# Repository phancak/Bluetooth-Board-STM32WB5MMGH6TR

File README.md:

# STM32WB5MMGH6TR Bluetooth Expansion Board  

## Overview  
This project features a **Bluetooth expansion board** based on the **STM32WB5MMGH6TR module**, designed for seamless integration with various embedded systems. The board provides flexible connectivity through **I2C, USART, and SPI**, making it an ideal solution for rapid prototyping and system expansion.  

Engineered for **low-power applications** and **high-performance wireless communication**, this board serves as a versatile platform for **IoT, industrial automation, and smart embedded devices**.  

## Features  
✅ **STM32WB5MMGH6TR Module** – Dual-core Cortex-M4/M0+ with BLE 5.2 support  
✅ **Multiple Communication Interfaces** – I2C, USART, and SPI for seamless integration  
✅ **Compact and Modular Design** – Easily integrates with other MCU-based projects  
✅ **Low-Power Optimization** – Suitable for battery-powered applications  
✅ **Expandable & Customizable** – Compatible with additional peripherals  

## Applications  
- **IoT Devices** – Wireless sensors, smart home automation  
- **Industrial Monitoring** – Data acquisition, remote control systems  
- **Embedded Systems Development** – Ideal for prototyping and experimentation  

## Getting Started  
### Hardware Requirements  
- STM32WB5MMGH6TR Bluetooth Expansion Board  
- Host MCU (STM32, ESP32, etc.)  
- Power Supply (3.3V)  
- Serial Debugging Tools (USB-to-Serial Adapter)  

### Software Requirements  
- **STM32CubeIDE** – For firmware development  
- **STM32CubeWB** – Bluetooth stack and middleware  
- **Segger J-Link or ST-Link** – For debugging and flashing  

## Setup & Usage  
1. **Power the Board** – Provide 3.3V via USB or external power source.  
2. **Connect to Host MCU** – Use I2C, USART, or SPI for communication.  
3. **Flash Firmware** – Use STM32CubeIDE or STM32CubeProgrammer.  
4. **Test Bluetooth Functionality** – Verify BLE communication using a mobile app or a central device.  

## Repository Structure  
/Hardware        - PCB schematics and design files  
  /Schematic      - Circuit diagrams (PDF, KiCad, Altium, etc.)  
  /PCB            - Board layout files (Gerber, BOM, assembly files)  

## Future Enhancements  
- 🔹 **Additional Protocol Support** – Expanding compatibility with more peripherals  
- 🔹 **Power Optimization** – Fine-tuning sleep modes for ultra-low power consumption  
- 🔹 **Custom BLE Services** – Implementing advanced communication features  

## License  
This project is open-source under the **MIT License**.  

---

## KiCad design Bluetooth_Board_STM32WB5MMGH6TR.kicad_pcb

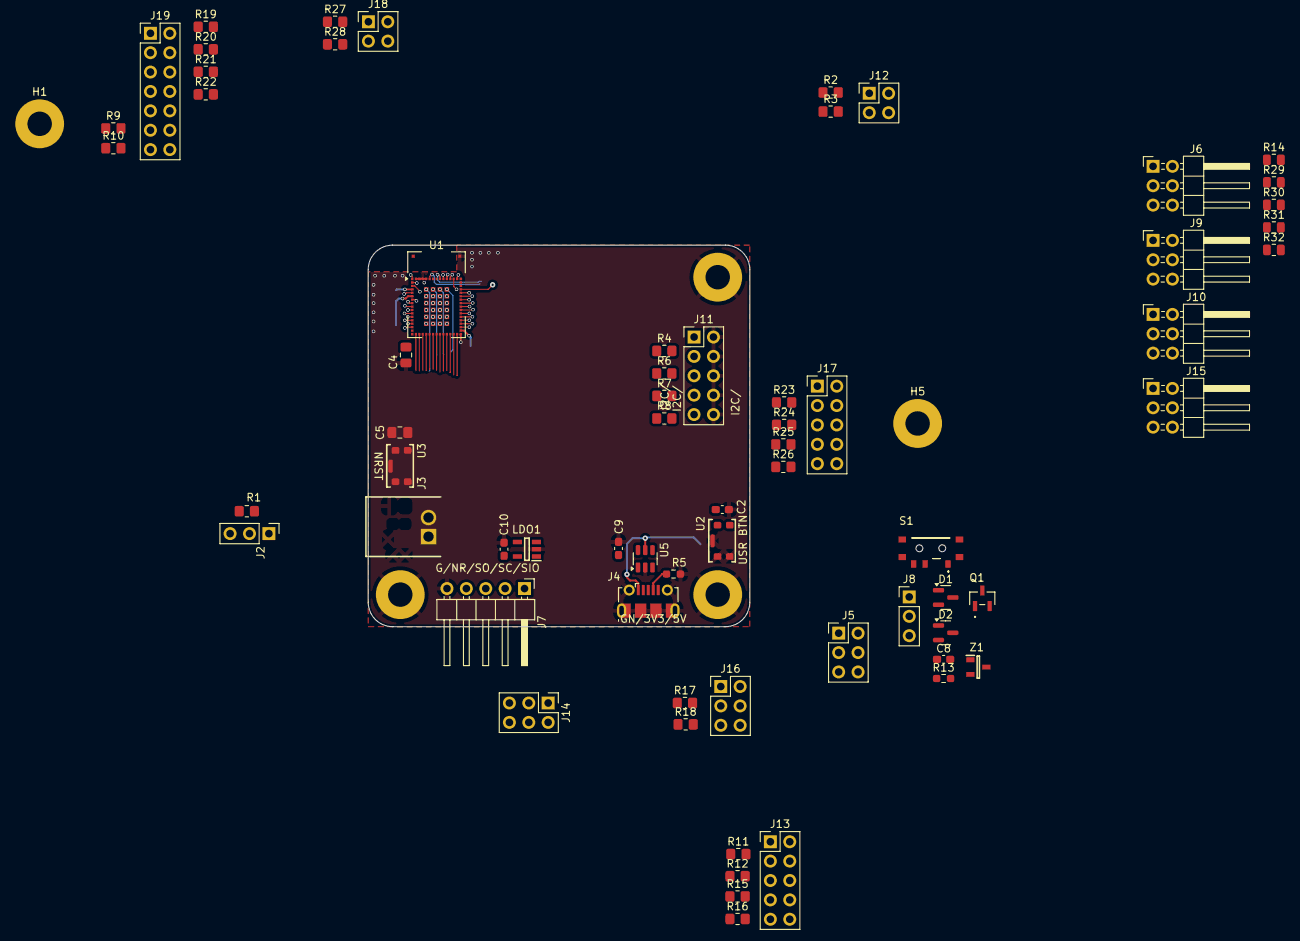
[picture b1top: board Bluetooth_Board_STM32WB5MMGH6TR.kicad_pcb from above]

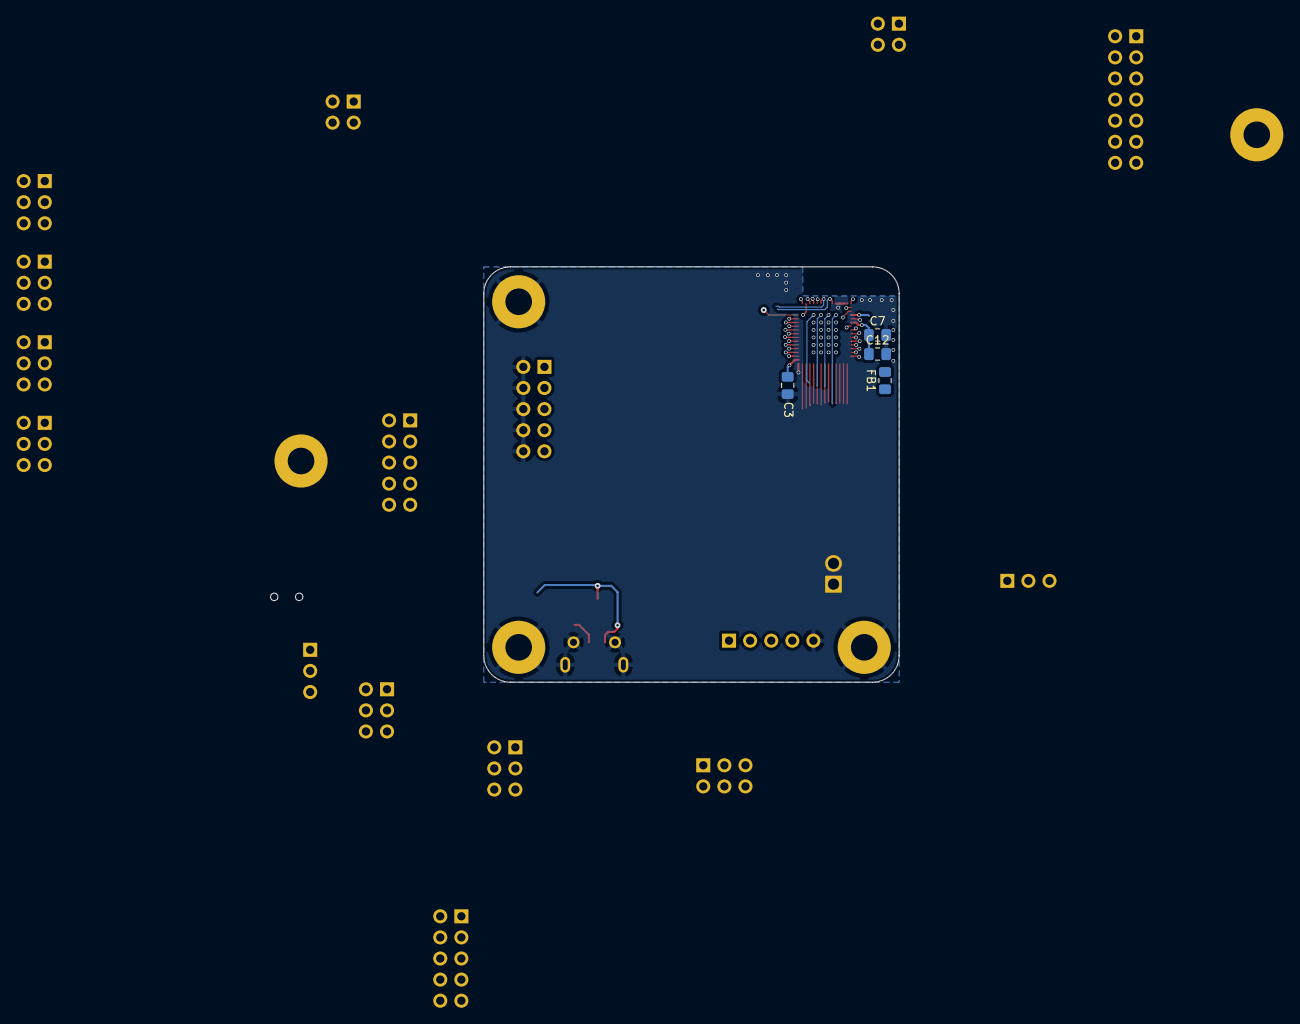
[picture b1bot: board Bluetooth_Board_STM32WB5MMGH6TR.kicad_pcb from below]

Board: 6 copper layers, 50.0 x 50.0 mm, 75 parts (4 on the bottom side), 79 nets.

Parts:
C2: 1uF; C_0603_1608Metric_Pad1.08x0.95mm_HandSolder
C3, C4, C7: 100n; C_0805_2012Metric_Pad1.18x1.45mm_HandSolder
C5: 100nF; C_0805_2012Metric_Pad1.18x1.45mm_HandSolder
C8: 4u7; C_0603_1608Metric_Pad1.08x0.95mm_HandSolder
C9, C10: 1u; C_0603_1608Metric_Pad1.08x0.95mm_HandSolder
C12: 4u7; C_0805_2012Metric_Pad1.18x1.45mm_HandSolder
D1: BZX84C4V3LT1G; SOT-23
D2: BZX84C6V2LT1G; SOT-23
FB1: BLM21PG601SN1D_0805; C_0805_2012Metric_Pad1.18x1.45mm_HandSolder
H1, H2, H3, H4, H5: MountingHole_Pad; MountingHole_3.2mm_M3_Pad
J2: BOOT0_Jumper; PinHeader_1x03_P2.54mm_Vertical
J3: JST_XH_2.54_Plug; Connector_Power2pin_SHDRRA2W80P0X250_1X2_740X1150X610P
J4: USB_B_Micro; USB_Micro-B_Molex-105017-0001
J5: Power_Selector_Jumper; PinHeader_2x03_P2.54mm_Vertical
J6: I2C1_Headers; PinHeader_2x03_P2.54mm_Horizontal
J7: SWD_Pins; PinHeader_1x05_P2.54mm_Horizontal
J8: 3V_Selection_Header; PinHeader_1x03_P2.54mm_Vertical
J9: LPUART1_Headers; PinHeader_2x03_P2.54mm_Horizontal
J10: SPI1_Headers; PinHeader_2x03_P2.54mm_Horizontal
J11: SPI1_Header; PinHeader_2x05_P2.54mm_Vertical
J12: TIM1_CH1_Headers; PinHeader_2x02_P2.54mm_Vertical
J13: SAI1_A_Header; PinHeader_2x05_P2.54mm_Vertical
J14: I2C1_Header; PinHeader_2x03_P2.54mm_Vertical
J15: General_Pin_Header; PinHeader_2x03_P2.54mm_Horizontal
J16: LPUART1_Header; PinHeader_2x03_P2.54mm_Vertical
J17: SAI1_B_Header; PinHeader_2x05_P2.54mm_Vertical
J18: ADC1_Headers; PinHeader_2x02_P2.54mm_Vertical
J19: QUADSPI_Header; PinHeader_2x07_P2.54mm_Vertical
LDO1: LDO_TLV75733PDBVR; LDO_SOT95P280X145-5N
Q1: MOSFET_SI2333DDS-T1-BE3; MOSFET_ SI2333DDS_SOT_DS-T1-BE3_VIS
R1: 1k; R_0805_2012Metric_Pad1.20x1.40mm_HandSolder
R2, R3, R4, R6, R7, R8, R9, R10, R11, R12, R15, R16, R17, R18, R19, R20, R21, R22, R23, R24, R25, R26, R27, R28: 100R; R_0805_2012Metric_Pad1.20x1.40mm_HandSolder
R5, R13: 100k; R_0603_1608Metric_Pad0.98x0.95mm_HandSolder
R14, R29, R30, R31, R32: 33R; R_0805_2012Metric
S1: Switch_WS-SLSU SMT Mini Slide
U1: STM32WB5MMGH6TR; ST-SiP-LGA-86-11x7.3mm
U2, U3: Button_KMR231GLFS
U5: USBLC6-2SC6; SOT-23-6
Z1: Diode_BZX84C6V2-7-F; Diode_BZX84C6V2_SOT96P240X110-3N

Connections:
+3.3V: C3.1, C4.1, FB1.1, J2.1, J11.1, J13.1, J14.1, J16.1, J17.1, J19.1, S1.2, U1.15 (VBAT), U1.17 (VDDSMPS), U1.32 (VDDUSB)
+5V: C9.1, LDO1.1 (IN), LDO1.3 (EN)
/BOOT0J: J2.2, R1.1
/EXT_POWER+: J3.2 (POWER+), Q1.3 (D)
/EXT_POWER+_NOLDO: J5.2, J8.1
/EXT_POWER+_PP: D1.3 (K), J5.1, J5.3, Q1.2 (S), Z1.3 (K)
/JTCK-SWCLK: J7.2, U1.26 (PA14)
/JTDO-TRACE-SWO: J7.3, U1.21 (PB3)
/JTMS-SWDIO: J7.1, U1.25 (PA13)
/LDO_IN: J5.4, J5.6
/LD_OUT_3V3: C10.1, J8.3, LDO1.5 (OUT)
/MOSFET_GATE: Q1.1 (G), R13.1, Z1.1 (A)
/NRST: C5.2, J7.4, U1.10 (NRST), U3.1, U3.2
/PA0_TIM2_CH1: R2.1, U1.3 (PA0)
/PA1_USR_BTN: C2.2, U1.2 (PA1), U2.1, U2.2
/PA2_LPUART1_TX: R14.2, R17.1, U1.1 (PA2)
/PA3_QUADSPI_CLK: R19.1, U1.56 (PA3)
/PA4_SAI1_FS_B: R23.1, U1.55 (PA4)
/PA5_SPI1_SCK: R4.1, U1.54 (PA5)
/PA6_SPI1_MISO: R7.1, U1.53 (PA6)
/PA7_SPI1_MOSI: R8.1, U1.52 (PA7)
/PA10_I2C1_SDA: J14.5, U1.28 (PA10)
/PA15_SPI1_NSS: R6.1, U1.27 (PA15)
/PB4_SAI1_MCLK_B: R26.1, U1.20 (PB4)
/PB5_SAI1_SD_B: R25.1, U1.19 (PB5)
/PB8_I2C1_SCL: J6.5, J14.3, U1.14 (PB8)
/PB9_QUADSPI_BK1_IO0: R21.1, U1.11 (PB9)
/PB10_LPUART1_RX: R18.1, U1.47 (PB10)
/PB11_QUADSPI_BK1_NCS: R20.1, U1.46 (PB11)
/PB12_SAI1_FS_A: R11.1, U1.41 (PB12)
/PB13_SAI1_SCK_A: R12.1, U1.35 (PB13)
/PB14_SAI1_MCLK_A: R16.1, U1.37 (PB14)
/PB15_SAI1_SD_A: R15.1, U1.38 (PB15)
/PC0_ADC1_IN1: R27.1, U1.12 (PC0)
/PC1_ADC1_IN2: R28.1, U1.9 (PC1)
/PC9_SAI1_SCK_B: R24.1, U1.69 (PC9)
/PD5_QUADSPI_BK1_IO1: R22.1, U1.80 (PD5)
/PD6_QUADSPI_BK1_IO2: R9.1, U1.81 (PD6)
/PD7_QUADSPI_BK1_IO3: R10.1, U1.67 (PD7)
/PD14_TIM1_CH1: R3.1, U1.63 (PD14)
/POWER_3V3: C8.1, J8.2, S1.1
/USB_D2+: J4.3 (D+), U5.3 (I/O2)
/USB_D2-: J4.2 (D-), U5.1 (I/O1)
/USB_D+: U1.29 (PA12), U5.4 (I/O2)
/USB_D-: U1.30 (PA11), U5.6 (I/O1)
/VBUS_5V: D2.3 (K), J4.1 (VBUS), J5.5, U5.5 (VBUS)
GND: C2.1, C3.2, C4.2, C5.1, C7.2, C8.2, C9.2, C10.2, C12.2, D1.1 (A), D2.1 (A), H1.1, H2.1, H3.1, H4.1, H5.1, J2.3, J3.1 (POWER-), J4.5 (GND), J4.6 (Shield), J6.2, J6.3, J6.4, J6.6, J7.5, J9.2, J9.3, J9.4, J9.6, J10.2, J10.6, J11.2, J11.4, J11.6, J11.8, J11.10, J12.2, J12.4, J13.2, J13.4, J13.6, J13.8, J13.10, J14.2, J14.4, J14.6, J15.1, J15.4, J15.5, J16.2, J16.4, J16.6, J17.2, J17.4, J17.6, J17.8, J17.10, J18.2, J18.4, J19.2, J19.4, J19.6, J19.8, J19.10, J19.12, J19.14, LDO1.2 (GND), R5.1, R13.2, U1.5 (VSS), U1.16 (VSSSMPS), U1.31 (VSS), U1.57 (VSS), U1.58 (ANT_IN), U1.59 (RF_OUT), U1.60 (VSS), U1.84 (VSS), U1.86 (VSS), U2.3, U2.4, U2.5 (GND), U3.3, U3.4, U3.5 (GND), U5.2 (GND)
unnamed: J4.4 (ID), R5.2
unnamed: J9.1, R14.1
unnamed: J9.5, R29.2
unnamed: J10.1, R30.2
unnamed: J10.4, R32.1
unnamed: J10.5, R31.2
unnamed: J11.3, R4.2
unnamed: J11.5, R6.2
unnamed: J11.7, R7.2
unnamed: J11.9, R8.2
unnamed: J12.1, R2.2
unnamed: J12.3, R3.2
unnamed: J13.3, R11.2
unnamed: J13.5, R12.2
unnamed: J13.7, R15.2
unnamed: J13.9, R16.2
unnamed: J16.3, R17.2
unnamed: J16.5, R18.2
unnamed: J17.3, R23.2
unnamed: J17.5, R24.2
unnamed: J17.7, R25.2
unnamed: J17.9, R26.2
unnamed: J18.1, R27.2
unnamed: J18.3, R28.2
unnamed: J19.3, R19.2
unnamed: J19.5, R20.2
unnamed: J19.7, R21.2
unnamed: J19.9, R22.2
unnamed: J19.11, R9.2
unnamed: J19.13, R10.2
unnamed: R1.2, U1.13 (PH3-BOOT0)
unnamed: C7.1, C12.1, FB1.2, U1.4 (VREF), U1.6 (VDDA)

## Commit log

2025-04-15 Pins selected
